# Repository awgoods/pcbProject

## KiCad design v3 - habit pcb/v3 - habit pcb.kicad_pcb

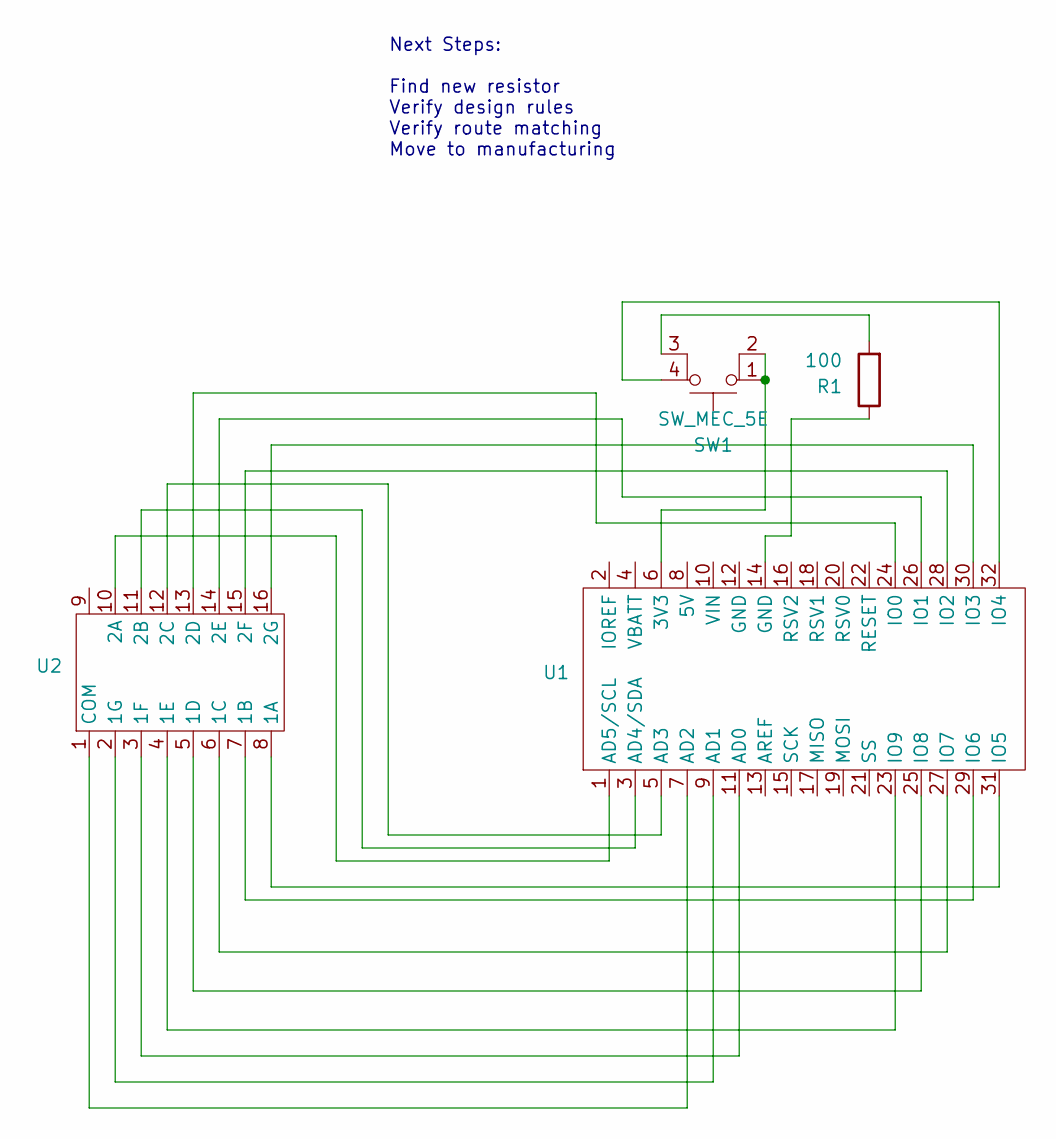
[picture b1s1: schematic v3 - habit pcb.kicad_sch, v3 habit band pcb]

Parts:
R1: 100; R_Axial_DIN0207_L6.3mm_D2.5mm_P10.16mm_Horizontal
SW1: SW_MEC_5E; DIP-4_177
U1: 32PinConnector
U2: LCD

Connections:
unnamed: R1.1, U1.14 (GND)
unnamed: SW1.4 (A), U1.32 (IO4)
unnamed: R1.2, SW1.3 (K)
unnamed: SW1.1, SW1.2, U1.6 (3V3)
unnamed: U1.11 (AD0), U2.3 (1F)
unnamed: U1.9 (AD1), U2.2 (1G)
unnamed: U1.7 (AD2), U2.1 (COM)
unnamed: U1.5 (AD3), U2.12 (2C)
unnamed: U1.3 (AD4/SDA), U2.11 (2B)
unnamed: U1.1 (AD5/SCL), U2.10 (2A)
unnamed: U1.24 (IO0), U2.13 (2D)
unnamed: U1.26 (IO1), U2.14 (2E)
unnamed: U1.28 (IO2), U2.15 (2F)
unnamed: U1.30 (IO3), U2.16 (2G)
unnamed: U1.31 (IO5), U2.8 (1A)
unnamed: U1.29 (IO6), U2.7 (1B)
unnamed: U1.27 (IO7), U2.6 (1C)
unnamed: U1.25 (IO8), U2.5 (1D)
unnamed: U1.23 (IO9), U2.4 (1E)

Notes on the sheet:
Next Steps: Find new resistor Verify design rules Verify route matching Move to manufacturing

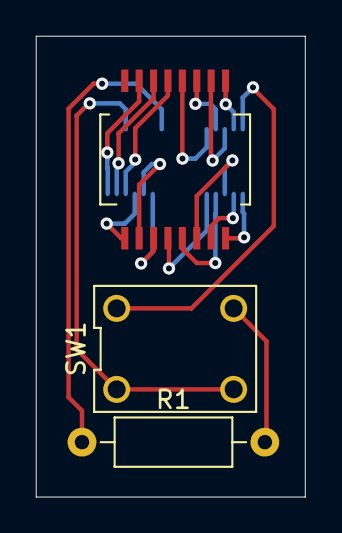
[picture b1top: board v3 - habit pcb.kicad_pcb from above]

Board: 2 copper layers, 15.0 x 25.6 mm, 4 parts (0 on the bottom side), 19 nets.
